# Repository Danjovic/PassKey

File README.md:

# PassKey
Keychain USB multiple password manager/generator/injector

This project provides an usb device to stor passwords that can be sent to your PC like keystrokes. 
It was inspired by USB Key Generator by Code & Life, and therefore is also based on AVR and V-USB.

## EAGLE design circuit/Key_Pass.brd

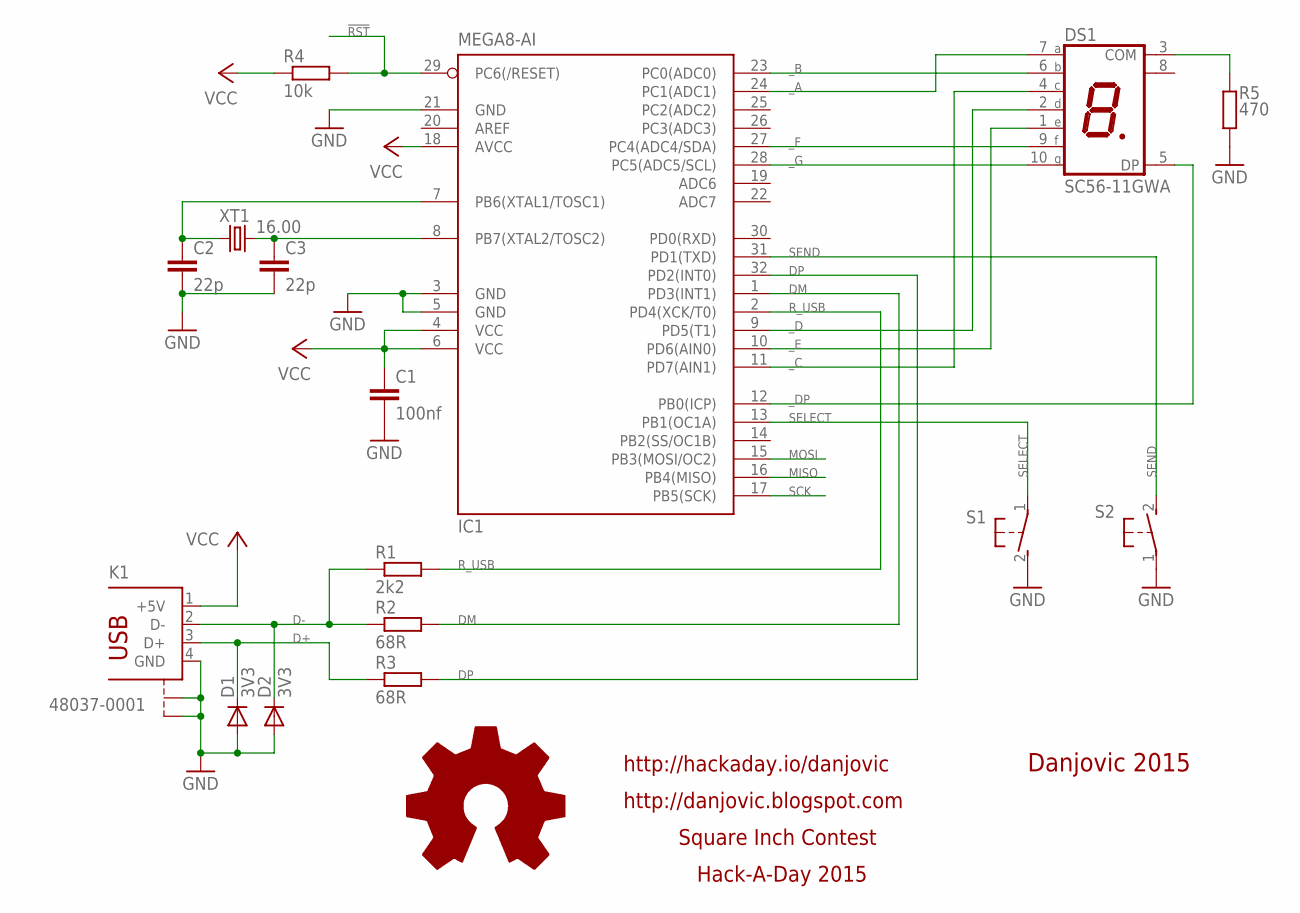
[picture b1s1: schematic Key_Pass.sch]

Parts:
C1: 100nf; C1206
C2, C3: 22p; C0805
D1, D2: 3V3; SOD80C
DS1: SC56-11GWA; SA52-11
IC1: MEGA8-AI; TQFP32-08
K1: 48037-0001
R1: 2k2; R0805
R2, R3: 68R; R0805
R4: 10k; R0805
R5: 470; R0805
S1, S2: 31-XX; B3F-31XX
XT1: 16.00; HC49UP

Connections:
!RST: IC1.29 (PC6(/RESET)), R4.2
D+: D1.C, K1.3 (D+), R3.1
D-: D2.C, K1.2 (D-), R1.1, R2.1
DM: IC1.1 (PD3(INT1)), R2.2
DP: IC1.32 (PD2(INT0)), R3.2
GND: C1.2, C2.1, C3.1, D1.A, D2.A, IC1.3 (GND), IC1.5 (GND), IC1.21 (GND), K1.4 (GND), K1.P$1 (S1), K1.P$2 (S2), R5.1, S1.2 (S), S2.1
MISO: IC1.16 (PB4(MISO))
MOSI: IC1.15 (PB3(MOSI/OC2))
unnamed: DS1.3 (COM), R5.2
unnamed: C2.2, IC1.7 (PB6(XTAL1/TOSC1)), XT1.1
R_USB: IC1.2 (PD4(XCK/T0)), R1.2
SCK: IC1.17 (PB5(SCK))
SELECT: IC1.13 (PB1(OC1A)), S1.1
SEND: IC1.31 (PD1(TXD)), S2.2 (S)
VCC: C1.1, IC1.4 (VCC), IC1.6 (VCC), IC1.18 (AVCC), K1.1 (+5V), R4.1
X1: C3.2, IC1.8 (PB7(XTAL2/TOSC2)), XT1.2
_A: DS1.7 (A), IC1.24 (PC1(ADC1))
_B: DS1.6 (B), IC1.23 (PC0(ADC0))
_C: DS1.4 (C), IC1.11 (PD7(AIN1))
_D: DS1.2 (D), IC1.9 (PD5(T1))
_DP: DS1.5 (DP), IC1.12 (PB0(ICP))
_E: DS1.1 (E), IC1.10 (PD6(AIN0))
_F: DS1.9 (F), IC1.27 (PC4(ADC4/SDA))
_G: DS1.10 (G), IC1.28 (PC5(ADC5/SCL))

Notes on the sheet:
Danjovic 2015
http://hackaday.io/danjovic
http://danjovic.blogspot.com
Square Inch Contest
Hack-A-Day 2015

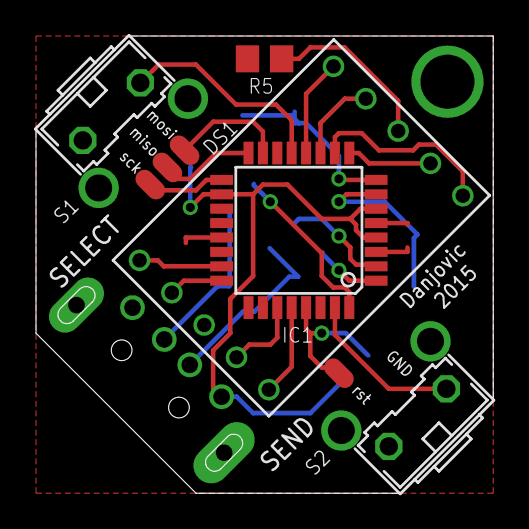
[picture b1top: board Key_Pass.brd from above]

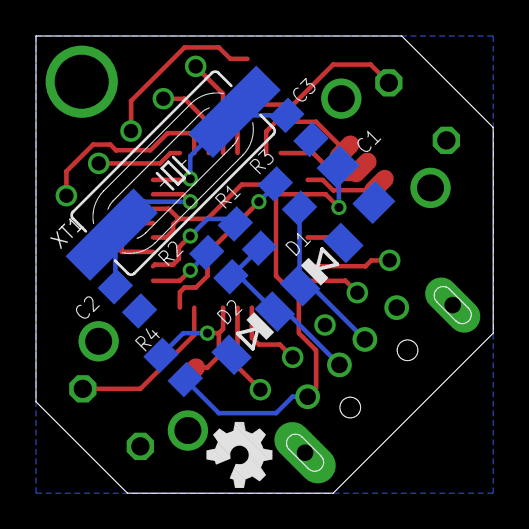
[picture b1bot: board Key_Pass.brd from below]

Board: 2 copper layers, 25.4 x 25.4 mm, 16 parts (10 on the bottom side), 21 nets.

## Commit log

2015-11-06 :confetti_ball: Added .gitattributes & .gitignore files
2015-11-06 Test Release
    First working version. Limitations:
    1) Bootloader activated by RESET
    2) Can not disable use of NUM LOCK / SCROLL LOCK
2015-11-12 Enabling/Disabling NUM_LOCK and SCROLL_LOCK; saving of last sent slot
    The functions to enable/disable alternative control by NUM LOCK (change
    slot) and SCROLL LOCK (send password) were added. Both configurations
    are saved in EEPROM, as well as the last slot number selected when a
    password was sent.
2015-11-13 Enter bootloader by press SELECT and SEND together
    Bootloader modified to enter in bootloader state when SELECT and SEND
    are both pressed when the device is inserted on USB port. After entering
    bootloader, the alternative activation by Num_Lock and Scroll_Lock are
    set by default as well as the current Slot is changed to '0' and the
    flag that indicates an Upload has occurred is set. This configuration is
    stored on the last address of EEPROM ( E2END )
2015-11-21 Ignore Eagle temp files
2015-11-28 Added License files
2015-12-03 Added script to support legacy passwords
2015-12-03 Named python script coherently to file generated
2015-12-07 Support for <CR> in legacy passwords file
